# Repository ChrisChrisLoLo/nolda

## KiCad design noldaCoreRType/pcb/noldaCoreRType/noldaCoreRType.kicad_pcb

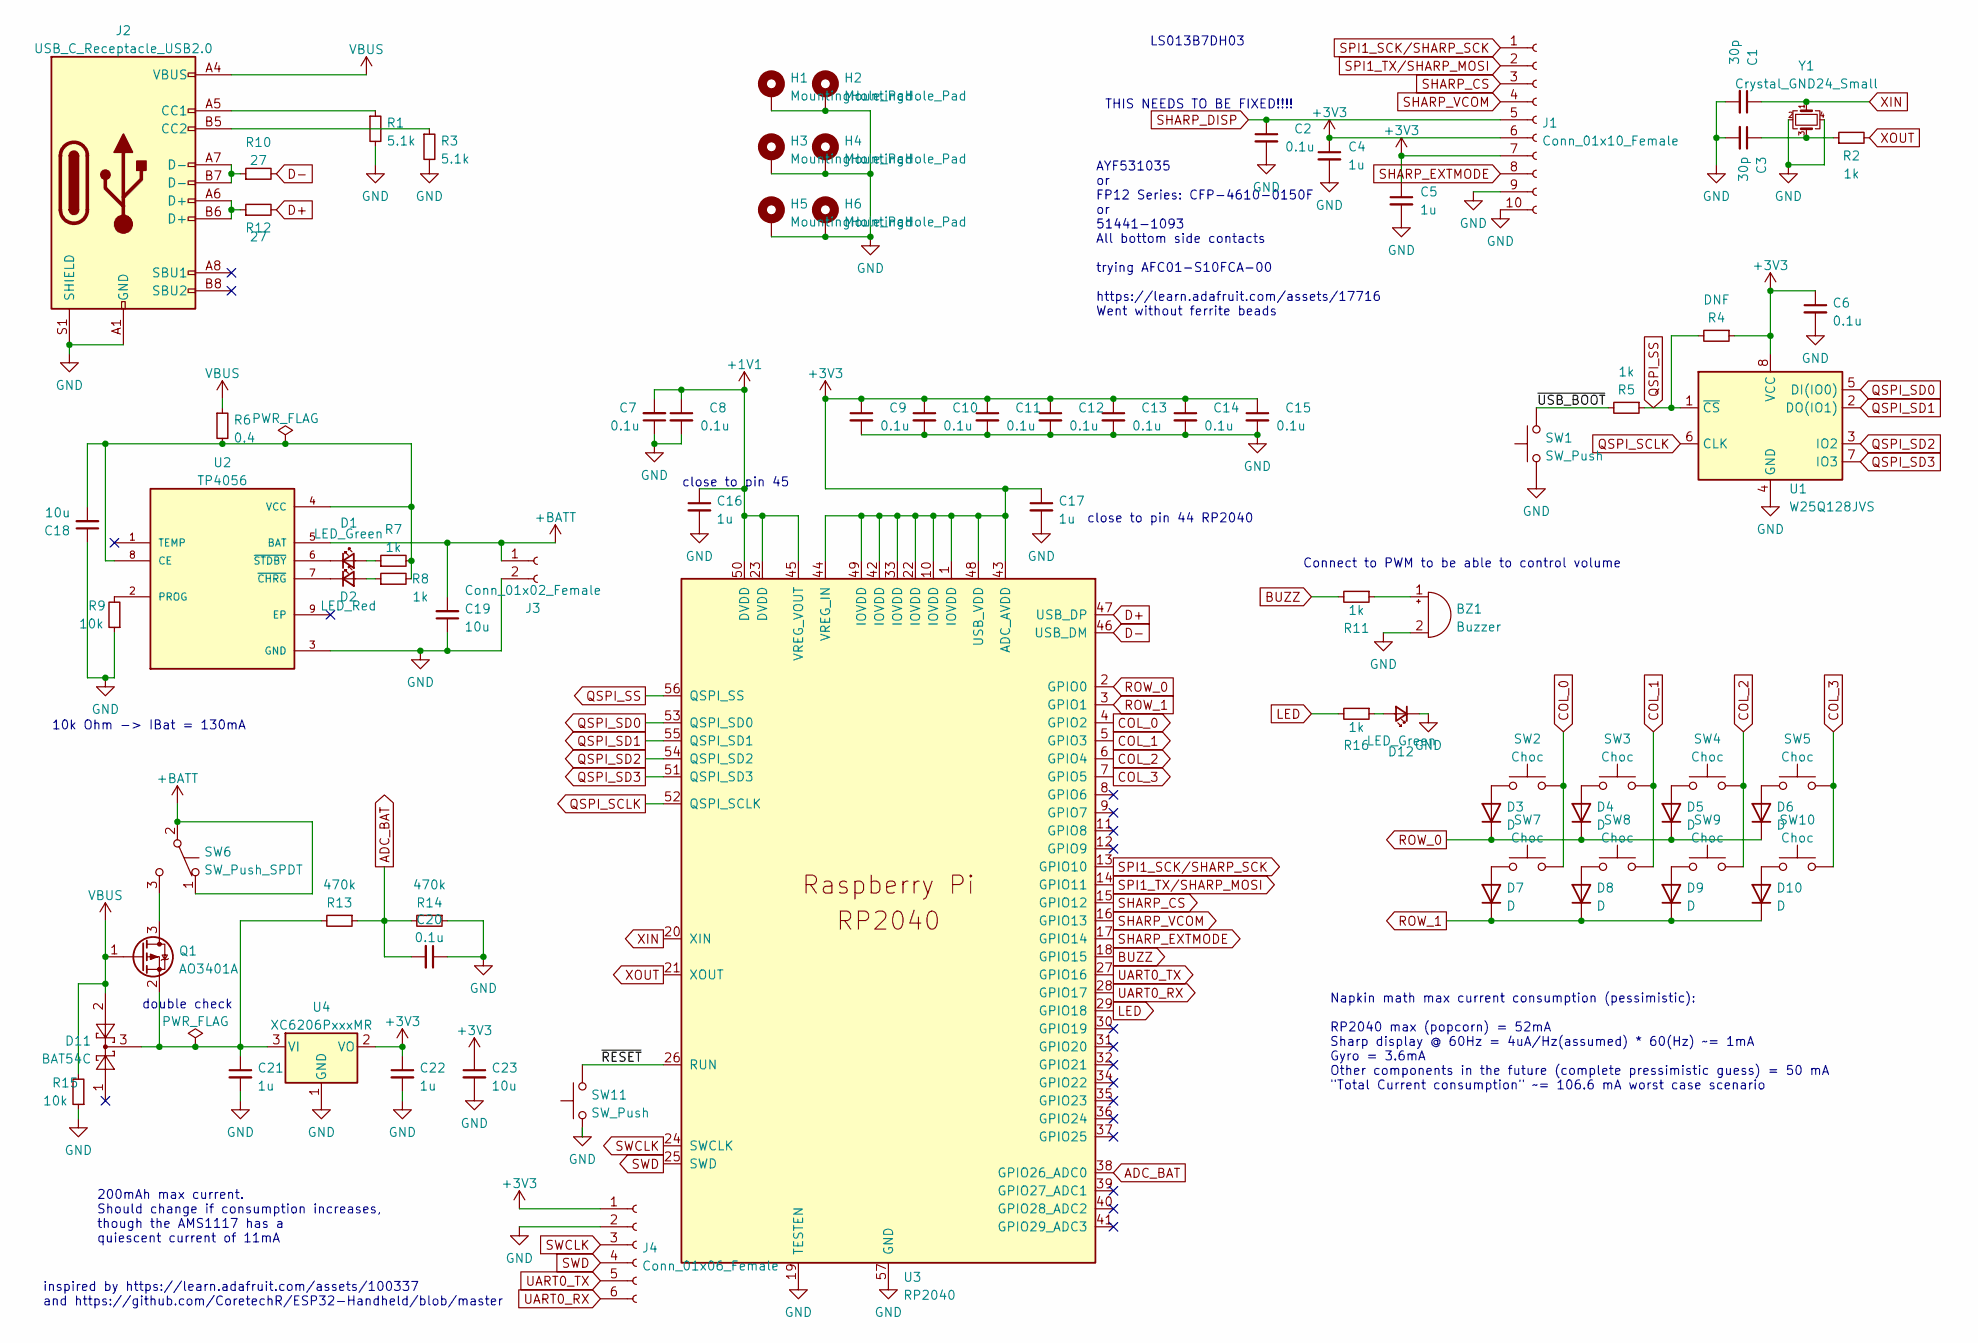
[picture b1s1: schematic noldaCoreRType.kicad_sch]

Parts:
BZ1: Buzzer; Buzzer_Murata_PKLCS1212E
C1, C3: 30p; C_0402_1005Metric
C2, C6, C7, C8, C9, C10, C11, C12, C13, C14, C15, C20: 0.1u; C_0402_1005Metric
C4, C5, C16, C17, C21, C22: 1u; C_0402_1005Metric
C18, C19, C23: 10u; C_0402_1005Metric
D1, D12: LED_Green; LED_0603_1608Metric
D2: LED_Red; LED_0603_1608Metric
D3, D4, D5, D6, D7, D8, D9, D10: D; D_SOD-123
D11: BAT54C; SOT-23
H1, H2, H3, H4, H5, H6: MountingHole_Pad; MountingHole_2.2mm_M2_ISO7380_Pad
J1: Conn_01x10_Female; Molex_54548-1071_1x10-1MP_P0.5mm_Horizontal
J2: USB_C_Receptacle_USB2.0; USB_C_Receptacle_XKB_U262-16XN-4BVC11
J3: Conn_01x02_Female; PinHeader_1x02_P2.00mm_Vertical
J4: Conn_01x06_Female; PinHeader_1x06_P2.54mm_Vertical
Q1: AO3401A; SOT-23
R1, R3: 5.1k; R_0402_1005Metric
R2, R5, R7, R8, R16: 1k; R_0402_1005Metric
R4: DNF; R_0402_1005Metric
R6: 0.4; R_0402_1005Metric
R9, R15: 10k; R_0402_1005Metric
R10, R12: 27; R_0402_1005Metric
R11: 1k; R_1206_3216Metric
R13, R14: 470k; R_0402_1005Metric
SW1, SW11: SW_Push; SW_SPST_TL3342
SW2, SW3, SW4, SW5, SW7, SW8, SW9, SW10: Choc; Kailh_socket_PG1350
SW6: SW_Push_SPDT; SW_SPDT_PCM12
U1: W25Q128JVS; SOIC-8_5.23x5.23mm_P1.27mm
U2: TP4056; SOP127P600X175-9N
U3: RP2040; RP2040-QFN-56
U4: XC6206PxxxMR; SOT-23
Y1: Crystal_GND24_Small; Crystal_SMD_3225-4Pin_3.2x2.5mm

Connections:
+1V1: C7.2, C8.1, C16.1, U3.23 (DVDD), U3.45 (VREG_VOUT), U3.50 (DVDD)
+BATT: C19.2, J3.1, SW6.1 (A), SW6.2 (B), U2.5 (BAT)
/~RESET: SW11.2, U3.26 (RUN)
/~USB_BOOT: R5.2, SW1.2
ADC_BAT: C20.2, R13.1, R14.2, U3.38 (GPIO26_ADC0)
BUZZ: R11.2, U3.18 (GPIO15)
COL_0: SW2.2, SW7.2, U3.4 (GPIO2)
COL_1: SW3.2, SW8.2, U3.5 (GPIO3)
COL_2: SW4.2, SW9.2, U3.6 (GPIO4)
COL_3: SW5.2, SW10.2, U3.7 (GPIO5)
D+: R12.2, U3.47 (USB_DP)
D-: R10.2, U3.46 (USB_DM)
GND: BZ1.2 (+), C1.2, C2.2, C3.2, C4.2, C5.2, C6.2, C7.1, C8.2, C9.2, C10.2, C11.2, C12.2, C13.2, C14.2, C15.2, C16.2, C17.2, C18.1, C19.1, C20.1, C21.2, C22.2, C23.2, D12.1 (K), H1.1, H2.1, H3.1, H4.1, H5.1, H6.1, J1.9, J1.10, J2.A1 (GND), J2.A12 (GND), J2.B1 (GND), J2.B12 (GND), J2.S1 (SHIELD), J3.2, J4.2, R1.2, R3.2, R9.1, R14.1, R15.1, SW1.1, SW11.1, U1.4 (GND), U2.3 (GND), U3.19 (TESTEN), U3.57 (GND), U4.1 (GND), Y1.2, Y1.4
LED: R16.2, U3.29 (GPIO18)
unnamed: BZ1.1 (-), R11.1
unnamed: C3.1, R2.1, Y1.3
unnamed: C18.2, R6.2, R7.2, R8.2, U2.4 (VCC), U2.8 (CE)
unnamed: C21.1, D11.3, Q1.2 (S), R13.2, U4.3 (VI)
unnamed: D1.1 (K), U2.6 (~STDBY)
unnamed: D1.2 (A), R7.1
unnamed: D2.1 (K), U2.7 (~CHRG)
unnamed: D2.2 (A), R8.1
unnamed: D3.2 (A), SW2.1
unnamed: D4.2 (A), SW3.1
unnamed: D5.2 (A), SW4.1
unnamed: D6.2 (A), SW5.1
unnamed: D7.2 (A), SW7.1
unnamed: D8.2 (A), SW8.1
unnamed: D9.2 (A), SW9.1
unnamed: D10.2 (A), SW10.1
unnamed: D12.2 (A), R16.1
unnamed: J2.A5 (CC1), R1.1
unnamed: J2.A6 (D+), J2.B6 (D+), R12.1
unnamed: J2.A7 (D-), J2.B7 (D-), R10.1
unnamed: J2.B5 (CC2), R3.1
unnamed: Q1.3 (D), SW6.3 (C)
unnamed: R9.2, U2.2 (PROG)
QSPI_SCLK: U1.6 (CLK), U3.52 (QSPI_SCLK)
QSPI_SD0: U1.5 (DI(IO0)), U3.53 (QSPI_SD0)
QSPI_SD1: U1.2 (DO(IO1)), U3.55 (QSPI_SD1)
QSPI_SD2: U1.3 (IO2), U3.54 (QSPI_SD2)
QSPI_SD3: U1.7 (IO3), U3.51 (QSPI_SD3)
QSPI_SS: R4.2, R5.1, U1.1 (~CS), U3.56 (QSPI_SS)
ROW_0: D3.1 (K), D4.1 (K), D5.1 (K), D6.1 (K), U3.2 (GPIO0)
ROW_1: D7.1 (K), D8.1 (K), D9.1 (K), D10.1 (K), U3.3 (GPIO1)
SHARP_CS: J1.3, U3.15 (GPIO12)
SHARP_EXTMODE: J1.8, U3.17 (GPIO14)
SHARP_VCOM: J1.4, U3.16 (GPIO13)
SPI1_SCK/SHARP_SCK: J1.1, U3.13 (GPIO10)
SPI1_TX/SHARP_MOSI: J1.2, U3.14 (GPIO11)
SWCLK: J4.3, U3.24 (SWCLK)
SWD: J4.4, U3.25 (SWD)
UART0_RX: J4.6, U3.28 (GPIO17)
UART0_TX: J4.5, U3.27 (GPIO16)
VBUS: D11.2, J2.A4 (VBUS), J2.A9 (VBUS), J2.B4 (VBUS), J2.B9 (VBUS), Q1.1 (G), R6.1, R15.2
XIN: C1.1, U3.20 (XIN), Y1.1
XOUT: R2.2, U3.21 (XOUT)

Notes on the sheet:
Connect to PWM to be able to control volume
inspired by https://learn.adafruit.com/assets/100337 and https://github.com/CoretechR/ESP32-Handheld/blob/master
10k Ohm -> IBat = 130mA
double check
THIS NEEDS TO BE FIXED!!!!
200mAh max current. Should change if consumption increases, though the AMS1117 has a quiescent current of 11mA
Napkin math max current consumption (pessimistic): RP2040 max (popcorn) = 52mA Sharp display @ 60Hz = 4uA/Hz(assumed) * 60(Hz) ~= 1mA Gyro = 3.6mA Other components in the future (complete pressimistic guess) = 50 mA "Total Current consumption" ~= 106.6 mA worst case scenario
LS013B7DH03
AYF531035 or FP12 Series: CFP-4610-0150F or 51441-1093 All bottom side contacts trying AFC01-S10FCA-00 https://learn.adafruit.com/assets/17716 Went without ferrite beads
close to pin 45
close to pin 44 RP2040

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
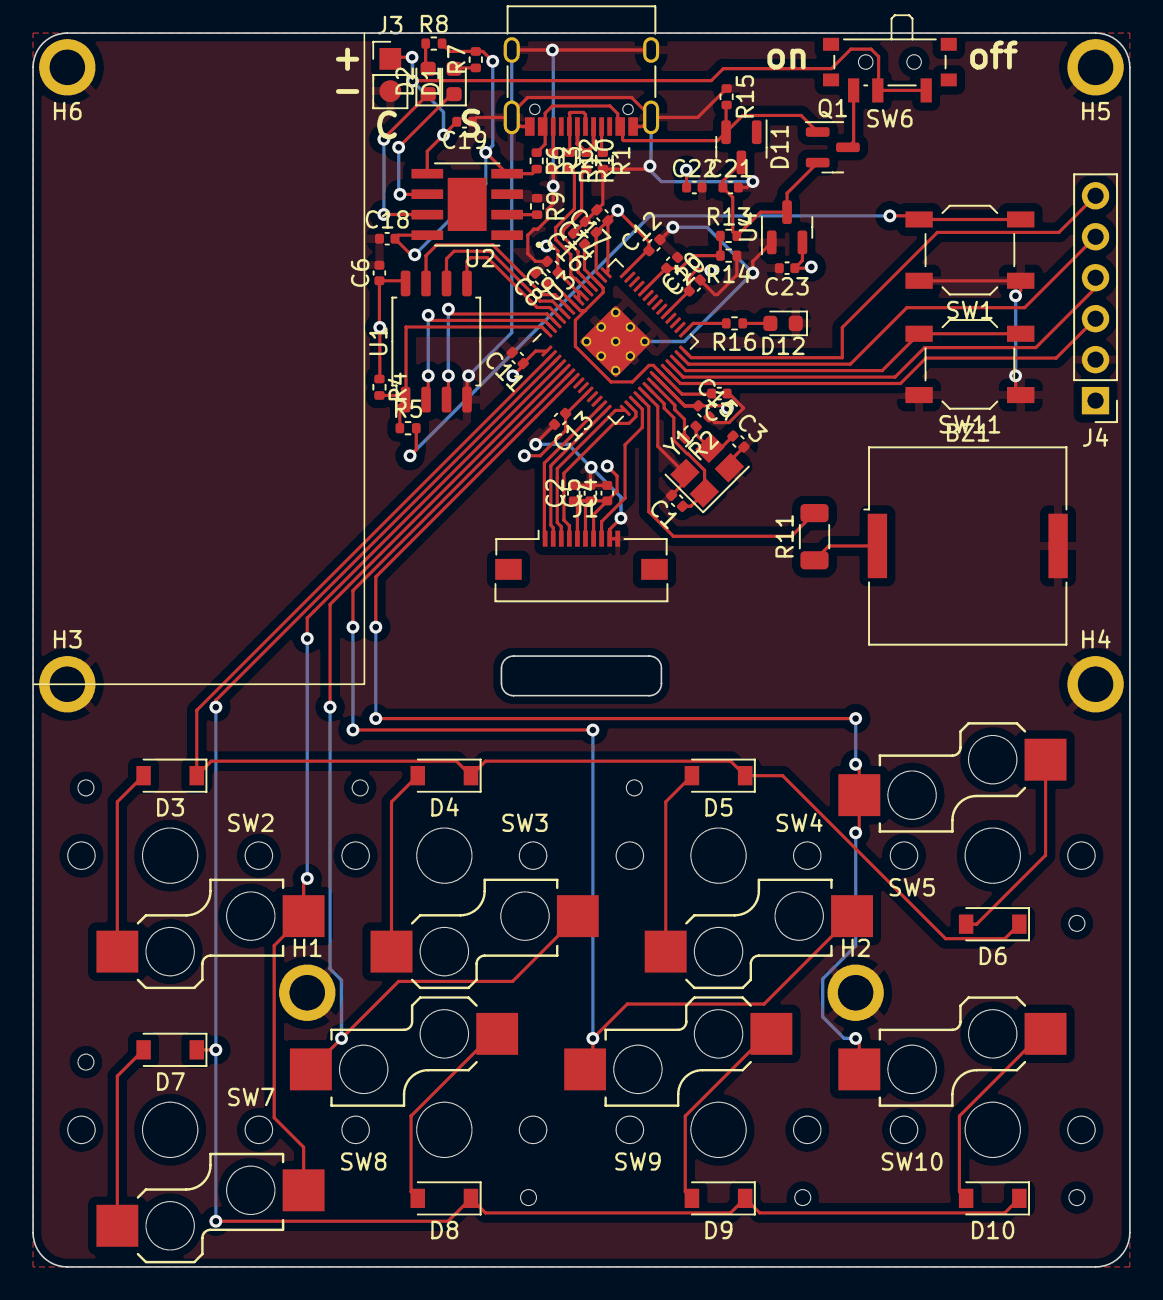
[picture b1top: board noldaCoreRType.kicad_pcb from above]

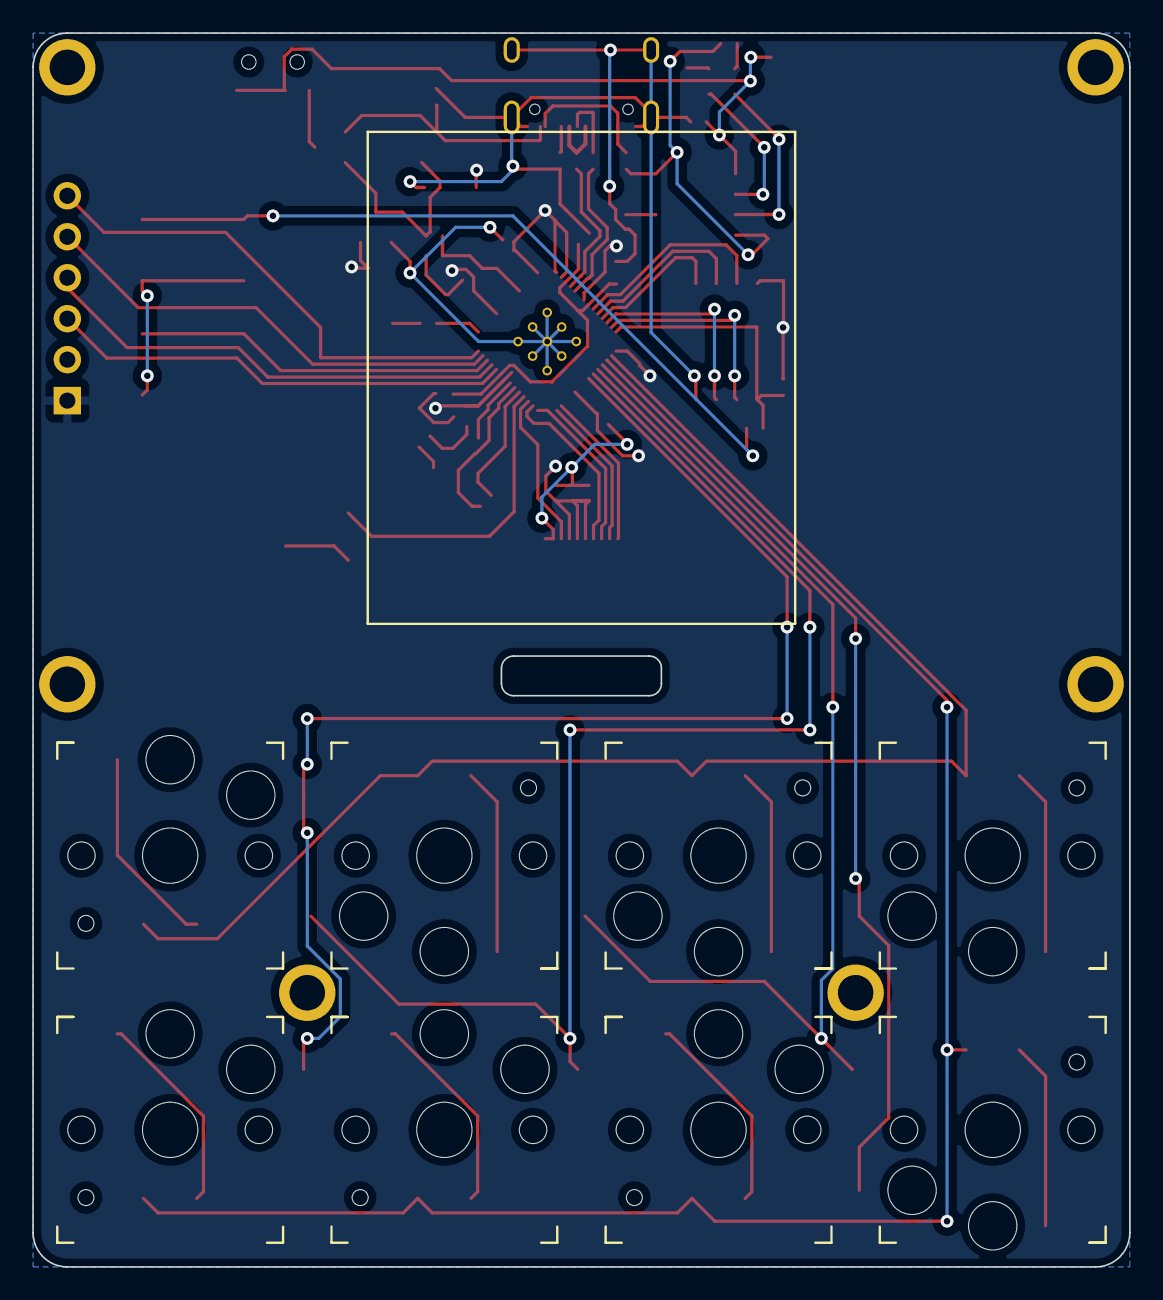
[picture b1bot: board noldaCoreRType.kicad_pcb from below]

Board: 2 copper layers, 68.0 x 76.5 mm, 79 parts (8 on the bottom side), 58 nets.

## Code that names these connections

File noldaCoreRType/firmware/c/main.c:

#include <FreeRTOS.h>
#include <queue.h>
#include <task.h>
#include <stdio.h>
#include <u8g2.h>
#include "pico/stdlib.h"
#include "hardware/gpio.h"
#include "hardware/spi.h"
#include <string.h>

u8g2_t u8g2;

// ADD THE INIT DISPLAY 
#define SPI_PORT spi1
#define PIN_CS 12
#define PIN_SCK 10
#define PIN_MOSI 11
#define SPI_SPEED 10 * 1000 * 1000

#define PIN_ROW_0 1
#define PIN_ROW_1 0
#define PIN_COL_0 2
#define PIN_COL_1 3
#define PIN_COL_2 4
#define PIN_COL_3 5

#define LED_PIN PICO_DEFAULT_LED_PIN
#define EXTMODE_PIN 14
#define VCOM_PIN 13

uint8_t u8x8_byte_pico_hw_spi(u8x8_t *u8x8, uint8_t msg, uint8_t arg_int, void *arg_ptr) {
  uint8_t *data;
  switch (msg) {
  case U8X8_MSG_BYTE_SEND:
    data = (uint8_t *)arg_ptr;
    spi_write_blocking(SPI_PORT, data, arg_int);
    break;
  case U8X8_MSG_BYTE_INIT:
    u8x8_gpio_SetCS(u8x8, u8x8->display_info->chip_disable_level);
    break;
  case U8X8_MSG_BYTE_SET_DC:
    u8x8_gpio_SetDC(u8x8, arg_int);
    break;
  case U8X8_MSG_BYTE_START_TRANSFER:
    u8x8_gpio_SetCS(u8x8, u8x8->display_info->chip_enable_level);
    u8x8->gpio_and_delay_cb(u8x8, U8X8_MSG_DELAY_NANO,u8x8->display_info->post_chip_enable_wait_ns, NULL);
    break;
  case U8X8_MSG_BYTE_END_TRANSFER:
    u8x8->gpio_and_delay_cb(u8x8, U8X8_MSG_DELAY_NANO,
                            u8x8->display_info->pre_chip_disable_wait_ns, NULL);
    u8x8_gpio_SetCS(u8x8, u8x8->display_info->chip_disable_level);
    break;
  default:
    return 0;
  }
  return 1;
}

uint8_t u8x8_gpio_and_delay_pico(u8x8_t *u8x8, uint8_t msg,uint8_t arg_int, void *arg_ptr) {
  switch (msg) {
  case U8X8_MSG_GPIO_AND_DELAY_INIT: 
    spi_init(SPI_PORT, SPI_SPEED);
    gpio_set_function(PIN_CS, GPIO_FUNC_SIO);
    gpio_set_function(PIN_SCK, GPIO_FUNC_SPI);
    gpio_set_function(PIN_MOSI, GPIO_FUNC_SPI);
    gpio_init(PIN_CS);
    gpio_set_dir(PIN_CS, GPIO_OUT);
    gpio_put(PIN_CS, 1);
    break;                  
  case U8X8_MSG_DELAY_NANO: // delay arg_int * 1 nano second
    sleep_us(arg_int);
    break;
  case U8X8_MSG_DELAY_100NANO: // delay arg_int * 100 nano seconds
    sleep_us(arg_int);
    break;
  case U8X8_MSG_DELAY_10MICRO: // delay arg_int * 10 micro seconds
    sleep_us(arg_int * 10);
    break;
  case U8X8_MSG_DELAY_MILLI: // delay arg_int * 1 milli second
    sleep_ms(arg_int);
    break;
  case U8X8_MSG_GPIO_CS: // CS (chip select) pin: Output level in arg_int
    gpio_put(PIN_CS, arg_int);
    break;
//   case U8X8_MSG_GPIO_DC: // DC (data/cmd, A0, register select) pin: Output level
//     gpio_put(PIN_DC, arg_int);
//     break;
//   case U8X8_MSG_GPIO_RESET: // Reset pin: Output level in arg_int
//     gpio_put(PIN_RST, arg_int);  // printf("U8X8_MSG_GPIO_RESET %d\n", arg_int);
//     break;
  default:
    u8x8_SetGPIOResult(u8x8, 1); // default return value
    break;
  }
  return 1;
}

void draw_display(char *message) {
	u8g2_ClearBuffer(&u8g2);
        u8g2_ClearDisplay(&u8g2);
	u8g2_SetDrawColor(&u8g2, 1);
        u8g2_SetFont(&u8g2, u8g2_font_t0_15_te);
        u8g2_DrawStr(&u8g2, 0, 10, message);
        u8g2_DrawStr(&u8g2, 0, 20, message);
        u8g2_DrawStr(&u8g2, 0, 40, message);
        u8g2_UpdateDisplay(&u8g2);
}

static const uint8_t msg_queue_len = 5;

static QueueHandle_t msg_queue;

// Used to refresh the screen to prevent polarization
// Can likely be moved to pio down the road
void refresh_screen_task()
{   
  draw_display("hello!");

  while (true) {
    gpio_put(LED_PIN, 1);
    gpio_put(VCOM_PIN, 1);

    vTaskDelay(200/portTICK_PERIOD_MS); // delay for 200 ms
    gpio_put(LED_PIN, 0);
    gpio_put(VCOM_PIN, 0);

    vTaskDelay(200/portTICK_PERIOD_MS);
  }
}

void draw_screen_task(){
  vTaskDelay(200/portTICK_PERIOD_MS); // deplay to allow screen to be setup. A bit sloppy, move init code to main

  int item;
  char message[32];

  while(true){
    if (xQueueReceive(msg_queue, (void *)&item, 0) == pdTRUE) {
      sprintf(message,"%d",item);
      draw_display(message);
    }
    vTaskDelay(100/portTICK_PERIOD_MS);
  }

}

#define KEY_MAP_ROW_LEN 2
#define KEY_MAP_COL_LEN 4 

int old_matrix_code = 0;
void read_keyboard_task()
{
  int rows[] = {PIN_ROW_0,PIN_ROW_1};
  int cols[] = {PIN_COL_0,PIN_COL_1,PIN_COL_2,PIN_COL_3};
  int row_len = (int) sizeof(rows) / sizeof(rows[0]);
  int col_len = (int) sizeof(cols) / sizeof(cols[0]);
  int keymap[KEY_MAP_ROW_LEN][KEY_MAP_COL_LEN] = {{1,2,3,4},{5,6,7,8}};

  for (int i=0; i<row_len; i++){
    gpio_init(rows[i]);
    gpio_set_dir(rows[i], GPIO_IN);
  }
  for (int i=0; i<col_len; i++){
    gpio_init(cols[i]);
    gpio_set_dir(cols[i], GPIO_OUT);
  }
  
  // scan
  int new_matrix_code = 0;
  while (true) {
    new_matrix_code = 0;
    for (int row_ind=0; row_ind<row_len; row_ind++){
      for (int col_ind=0; col_ind<col_len; col_ind++){
        gpio_put(cols[col_ind], 1);
        //printf("powering pin:%i\n", cols[col_ind]);
        vTaskDelay(5/portTICK_PERIOD_MS); // debounce
        bool is_key_pressed = gpio_get(rows[row_ind]);
        //printf("got %i from %i pin\n", gpio_get(rows[row_ind]), rows[row_ind]);
        new_matrix_code <<= 1; // convert matrix to binary bytes represented as int 
        new_matrix_code += is_key_pressed;
        gpio_put(cols[col_ind],0);
      }
    }
    printf("new matrix code:%i\n", new_matrix_code);
    if (new_matrix_code != old_matrix_code){
      if (xQueueSend(msg_queue, &new_matrix_code, 10) != pdTRUE){
        // error
      };
      old_matrix_code = new_matrix_code;
    }
    vTaskDelay(100/portTICK_PERIOD_MS);
  }
}

int main()
{
    stdio_init_all();
    printf("Board init!\n");

    // // attempt to reset spi bus
    // gpio_init(PIN_CS);
    // gpio_set_dir(PIN_CS, GPIO_OUT);
    // gpio_put(PIN_CS, 0);
    // sleep_us(100);
    // //


    gpio_init(LED_PIN);
    gpio_init(EXTMODE_PIN);
    gpio_init(VCOM_PIN);

    gpio_set_dir(LED_PIN, GPIO_OUT);
    gpio_set_dir(EXTMODE_PIN, GPIO_OUT);
    gpio_set_dir(VCOM_PIN, GPIO_OUT);

    gpio_put(EXTMODE_PIN, 1);   // enable extmode
    gpio_put(VCOM_PIN, 1);
    gpio_put(LED_PIN, 1);

    u8g2_Setup_ls013b7dh03_128x128_f(&u8g2, U8G2_R0, u8x8_byte_pico_hw_spi, u8x8_gpio_and_delay_pico);
    u8g2_InitDisplay(&u8g2);
    u8g2_SetPowerSave(&u8g2, 0);

    msg_queue = xQueueCreate(msg_queue_len, sizeof(int));

    xTaskCreate(refresh_screen_task, "Refresh_Screen_Task", 256, NULL, 1, NULL);
    xTaskCreate(read_keyboard_task, "Read_Keyboard_Task", 2000, NULL, 1, NULL);
    xTaskCreate(draw_screen_task, "Draw_Screen_Task", 256, NULL, 1, NULL);

    vTaskStartScheduler();

    while(1){};
}

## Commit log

2023-04-08 init commit
2023-04-16 add outlines
2023-04-17 add submodules
2023-04-23 code init (?)
2023-04-23 update C firmware
2023-04-23 add freertos
2023-04-23 fixup gitignore
2023-04-23 add u8g2
2023-04-24 add hello world u8g2
2023-04-24 add vcom refresh
2023-04-24 arduino sketch so I don't lose it
2023-04-24 add back in screen. oops!
2023-04-24 fix display bug where only portion of screen got updated
2023-05-08 add basic keyscanning
